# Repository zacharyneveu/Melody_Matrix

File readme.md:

# Melody Matrix

## Team
+ Connor
+ Yiwen
+ Kelvin 
+ Teng
+ Zach
+ Andreas

## About

## Organization
Each topic is put into a subfolder. Topics include:

+ Audio Programming (stuff on the Raspberry Pi)
+ Machine Learning (model code etc.)
+ Visualization (driver and artistic parts)

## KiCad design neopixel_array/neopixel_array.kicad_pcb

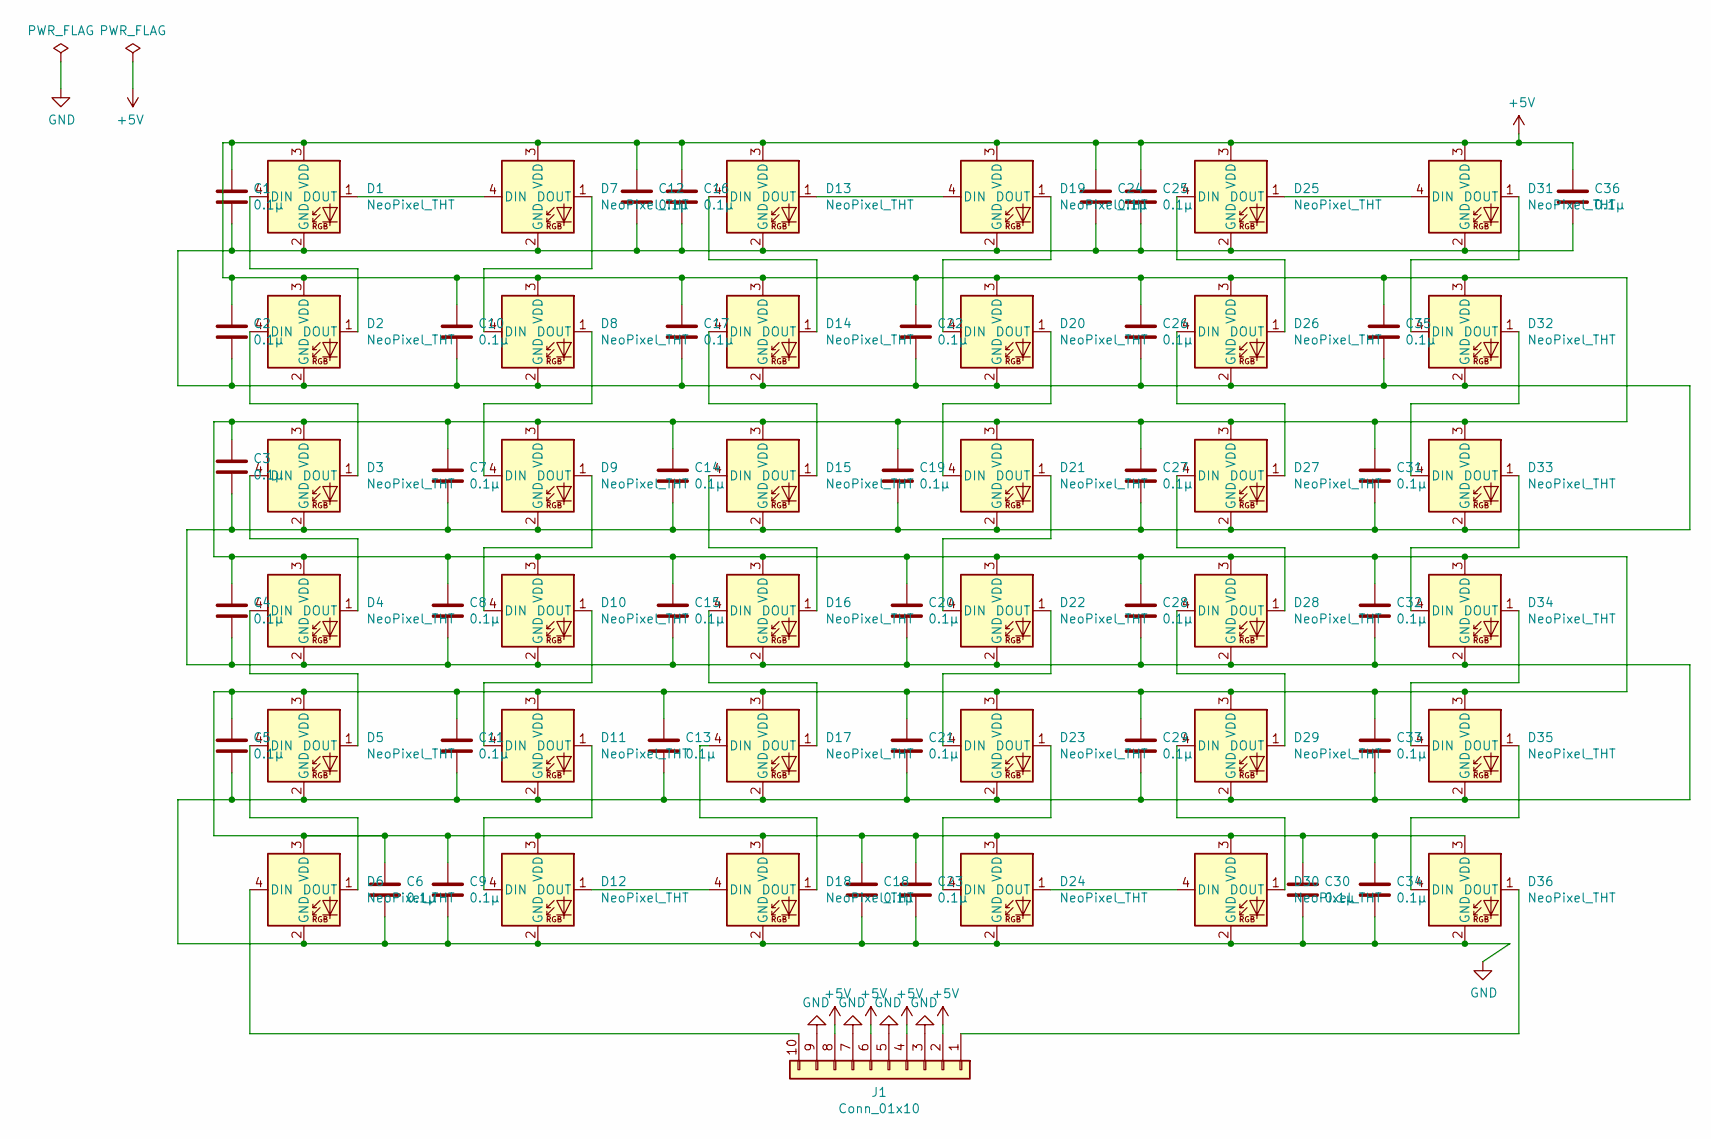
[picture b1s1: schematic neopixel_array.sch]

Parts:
C1, C2, C3, C4, C5, C6, C7, C8, C9, C10, C11, C12, C13, C14, C15, C16, C17, C18, C19, C20, C21, C22, C23, C24, C25, C26, C27, C28, C29, C30, C31, C32, C33, C34, C35, C36: 0.1µ; C_0805_2012Metric_Pad1.15x1.40mm_HandSolder
D1, D2, D3, D4, D5, D6, D7, D8, D9, D10, D11, D12, D13, D14, D15, D16, D17, D18, D19, D20, D21, D22, D23, D24, D25, D26, D27, D28, D29, D30, D31, D32, D33, D34, D35, D36: NeoPixel_THT; LED_D5.0mm-4_RGB
J1: Conn_01x10; TerminalBlock_4Ucon_1x10_P3.50mm_Horizontal

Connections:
+5V: C1.1, C2.1, C3.1, C4.1, C5.1, C6.1, C7.1, C8.1, C9.1, C10.1, C11.1, C12.1, C13.1, C14.1, C15.1, C16.1, C17.1, C18.1, C19.1, C20.1, C21.1, C22.1, C23.1, C24.1, C25.1, C26.1, C27.1, C28.1, C29.1, C30.1, C31.1, C32.1, C33.1, C34.1, C35.1, C36.1, D1.3 (VDD), D2.3 (VDD), D3.3 (VDD), D4.3 (VDD), D5.3 (VDD), D6.3 (VDD), D7.3 (VDD), D8.3 (VDD), D9.3 (VDD), D10.3 (VDD), D11.3 (VDD), D12.3 (VDD), D13.3 (VDD), D14.3 (VDD), D15.3 (VDD), D16.3 (VDD), D17.3 (VDD), D18.3 (VDD), D19.3 (VDD), D20.3 (VDD), D21.3 (VDD), D22.3 (VDD), D23.3 (VDD), D24.3 (VDD), D25.3 (VDD), D26.3 (VDD), D27.3 (VDD), D28.3 (VDD), D29.3 (VDD), D30.3 (VDD), D31.3 (VDD), D32.3 (VDD), D33.3 (VDD), D34.3 (VDD), D35.3 (VDD), D36.3 (VDD), J1.2, J1.4, J1.6, J1.8
GND: C1.2, C2.2, C3.2, C4.2, C5.2, C6.2, C7.2, C8.2, C9.2, C10.2, C11.2, C12.2, C13.2, C14.2, C15.2, C16.2, C17.2, C18.2, C19.2, C20.2, C21.2, C22.2, C23.2, C24.2, C25.2, C26.2, C27.2, C28.2, C29.2, C30.2, C31.2, C32.2, C33.2, C34.2, C35.2, C36.2, D1.2 (GND), D2.2 (GND), D3.2 (GND), D4.2 (GND), D5.2 (GND), D6.2 (GND), D7.2 (GND), D8.2 (GND), D9.2 (GND), D10.2 (GND), D11.2 (GND), D12.2 (GND), D13.2 (GND), D14.2 (GND), D15.2 (GND), D16.2 (GND), D17.2 (GND), D18.2 (GND), D19.2 (GND), D20.2 (GND), D21.2 (GND), D22.2 (GND), D23.2 (GND), D24.2 (GND), D25.2 (GND), D26.2 (GND), D27.2 (GND), D28.2 (GND), D29.2 (GND), D30.2 (GND), D31.2 (GND), D32.2 (GND), D33.2 (GND), D34.2 (GND), D35.2 (GND), D36.2 (GND), J1.3, J1.5, J1.7, J1.9
unnamed: D1.1 (DOUT), D7.4 (DIN)
unnamed: D1.4 (DIN), D2.1 (DOUT)
unnamed: D2.4 (DIN), D3.1 (DOUT)
unnamed: D3.4 (DIN), D4.1 (DOUT)
unnamed: D4.4 (DIN), D5.1 (DOUT)
unnamed: D5.4 (DIN), D6.1 (DOUT)
unnamed: D6.4 (DIN), J1.10
unnamed: D7.1 (DOUT), D8.4 (DIN)
unnamed: D8.1 (DOUT), D9.4 (DIN)
unnamed: D10.1 (DOUT), D11.4 (DIN)
unnamed: D9.1 (DOUT), D10.4 (DIN)
unnamed: D11.1 (DOUT), D12.4 (DIN)
unnamed: D12.1 (DOUT), D18.4 (DIN)
unnamed: D13.1 (DOUT), D19.4 (DIN)
unnamed: D13.4 (DIN), D14.1 (DOUT)
unnamed: D14.4 (DIN), D15.1 (DOUT)
unnamed: D15.4 (DIN), D16.1 (DOUT)
unnamed: D16.4 (DIN), D17.1 (DOUT)
unnamed: D17.4 (DIN), D18.1 (DOUT)
unnamed: D19.1 (DOUT), D20.4 (DIN)
unnamed: D20.1 (DOUT), D21.4 (DIN)
unnamed: D21.1 (DOUT), D22.4 (DIN)
unnamed: D22.1 (DOUT), D23.4 (DIN)
unnamed: D23.1 (DOUT), D24.4 (DIN)
unnamed: D24.1 (DOUT), D30.4 (DIN)
unnamed: D25.1 (DOUT), D31.4 (DIN)
unnamed: D25.4 (DIN), D26.1 (DOUT)
unnamed: D26.4 (DIN), D27.1 (DOUT)
unnamed: D27.4 (DIN), D28.1 (DOUT)
unnamed: D28.4 (DIN), D29.1 (DOUT)
unnamed: D29.4 (DIN), D30.1 (DOUT)
unnamed: D31.1 (DOUT), D32.4 (DIN)
unnamed: D32.1 (DOUT), D33.4 (DIN)
unnamed: D33.1 (DOUT), D34.4 (DIN)
unnamed: D34.1 (DOUT), D35.4 (DIN)
unnamed: D35.1 (DOUT), D36.4 (DIN)
unnamed: D36.1 (DOUT), J1.1

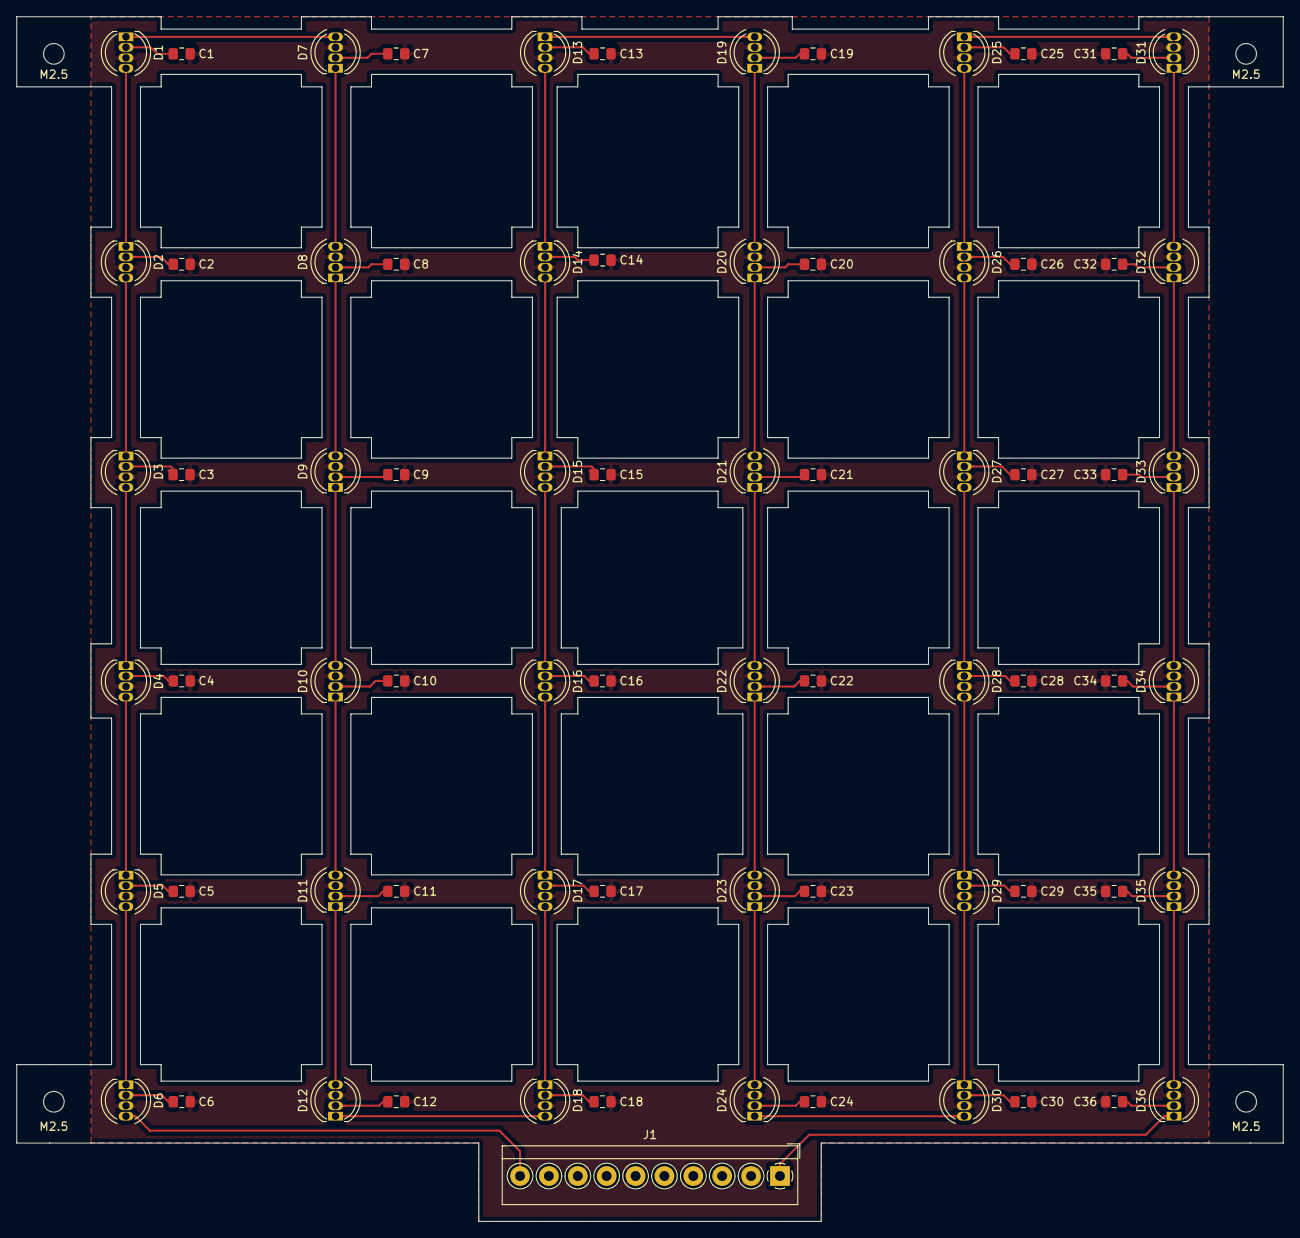
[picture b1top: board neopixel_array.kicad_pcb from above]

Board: 2 copper layers, 153.5 x 146.0 mm, 77 parts (0 on the bottom side), 39 nets.

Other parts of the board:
M2.5, M2.5#2, M2.5#3, M2.5#4: MountingHole_2.5mm

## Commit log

2020-01-20 add some machine learning stuff
2020-01-21 add genre classifier beginnings '
2020-01-21 add cover scraping code
2020-01-22 add color stuff to ml
2020-01-26 Added project
2020-01-26 Ordered the PCB using the gerber files
2020-01-28 add latest work
2020-02-11 adaptations to machine learning
2020-02-11 Adaptation for ML to Arudino
    color_node_2 and midi_note are external dictionary files
2020-02-11 Merged version1.py with main.py
2020-02-11 Minor updates on comments
2020-02-13 updated pcb with svg files
2020-02-13 add a bunch of note classifier stuff
2020-02-15 add latest work for desktop transfer
2020-02-19 New functions for brightness and channel visualization
2020-02-20 Added test array generator
2020-02-20 Added 2nd method of brightness visualization
2020-02-20 pushing arduino code
2020-02-21 add newest code and models
2020-02-22 adding separate py files for jetson
2020-02-22 added inference basics
2020-02-22 Python to arduino test code
2020-02-22 zach modify visuals code '
2020-02-23 Add docstrings to functions
2020-02-23 add better color determination, flip screen display '
2020-02-23 Change all hex_code to color_string
2020-02-23 Remove midi_note
2020-02-23 Upload color_code with #
2020-02-24 Adding Connor's work on the arduino side
2020-02-24 Update kelvin's codes which copies Connor's code and updates the copy with the gamma correction
2020-02-24 remove one extra part
2020-02-25 Modified test_array_generator()
2020-02-25 send array accepts frame rate
2020-03-15 added folder for web app
2020-03-15 Added Guide.txt
2020-03-15 Modified the text
2020-03-15 Get rid of comments
2020-03-16 Adding electron web app
2020-03-19 Added basic camera functionality
2020-03-19 Added random frames rendering feature
2020-03-19 Added function for resize feature
2020-03-20 drop-down list(version 1)
2020-03-20 typo fixed
2020-03-20 fixed camera controls
2020-03-20 updating work
2020-03-21 Update electron app's libraries so camera functionalities work
2020-03-21 Small change to easycam distance
2020-03-22 erased duplicate easycam creation
2020-03-23 updated gitignore
2020-03-23 implemented mic input
2020-03-23 npm audit
2020-03-23 removed resources folder
2020-03-23 removed sketch.js
2020-03-23 added colors and audio files as assets
2020-03-23 basic audio response
2020-03-24 add exported ml models
2020-03-24 add drop-down list for audio inputs (supports mic input)
2020-03-24 implemented normalized energy. Need to scale brightness
2020-03-25 Added visualization method in JS
2020-03-25 Modified getY()
2020-03-25 Refactoring electron app to use an MVC structure
2020-03-25 cube no longer needs to reset. turned down volume
2020-03-25 implemented energy scaling for sphere size
2020-03-26 removed sfile demo
2020-03-26 implemented sound reactivity in the MVC
2020-03-26 Calculation out of draw()
2020-03-27 it works but certain regions of the cube seem unreachable...
2020-03-27 now the matrix_array is updated
2020-03-27 adjusted threshold and fixed y mapping
2020-03-27 Matrix type: string -> int
2020-03-27 Adding in timer function to controller
2020-03-27 Some of the changes from when i added in the timer didn't commit for some reason
2020-03-27 Fixed timer (as best I could)
2020-03-28 added random genre renering test method
2020-03-28 add latest changes
2020-03-29 add ml basics
2020-03-29 working genre classifier
2020-03-30 Added color picker feature
2020-03-30 commented on the global variable useCustom
2020-03-30 remove local model and extra logging
2020-03-30 Added toggleCustom function
2020-03-31 adjusted z-pos to wrap around. it workes a bit better with the new y mapping
2020-03-31 removed sphere demo2
2020-03-31 removed unused value limit function
2020-03-31 add fullscreen / new window size support
2020-03-31 support audio input selections (auto input-detection)
2020-03-31 add audio selection box
2020-04-10 color picker displays and "works", but won't update colors
2020-04-10 updated detect arduino
2020-04-10 trying to get stuff working on my end
2020-04-10 Fixed color picker
